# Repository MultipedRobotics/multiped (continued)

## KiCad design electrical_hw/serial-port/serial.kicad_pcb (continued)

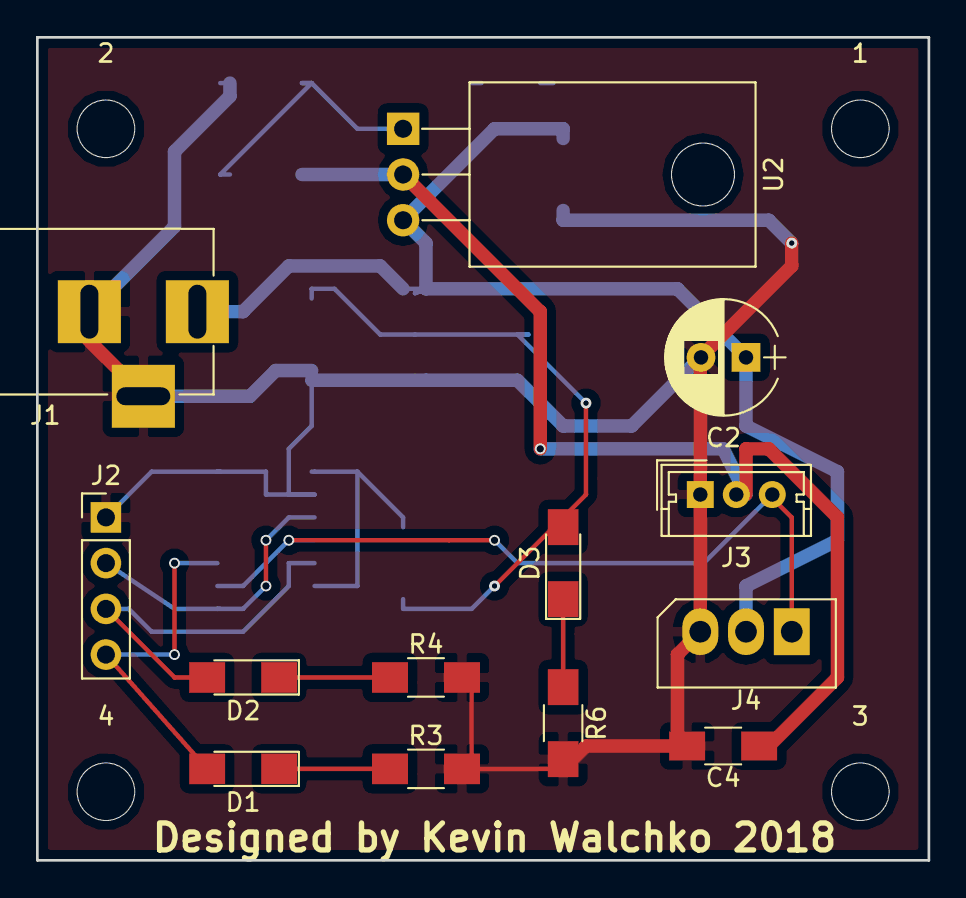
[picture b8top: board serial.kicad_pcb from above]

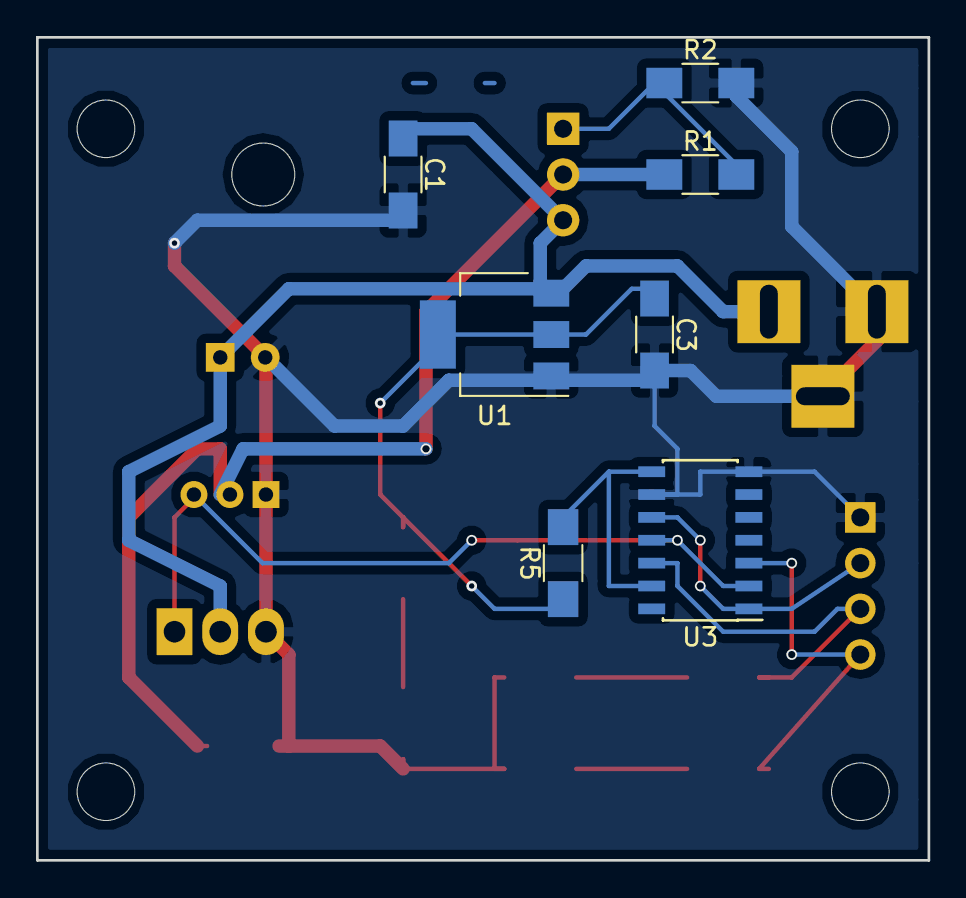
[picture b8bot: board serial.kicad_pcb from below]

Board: 2 copper layers, 49.5 x 45.7 mm, 24 parts (7 on the bottom side), 13 nets.

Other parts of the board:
1, 2, 3, 4: MountingHole_3.2mm_M3

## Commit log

2017-07-10 init
2017-07-10 bulk move of docs folder
2017-07-10 refactor docs
2017-07-10 winning! :smiley_cat:
2017-07-10 update ... added hardware
2017-07-11 fixed test
2017-07-11 code cleanup
2017-07-11 codacy
2017-07-11 upate
2017-07-12 added new gaits
2017-07-13 robot?
2017-07-13 readme and bin fix
2017-07-13 creating classes
2017-07-20 jupyter notebook
2017-12-03 working
2017-12-03 removed numpy
2017-12-25 reorg ... test still fail
2018-02-04 image link
2018-02-04 hardware updates
2018-02-04 pi zero clean-up
2018-02-04 fix build script
2018-02-04 readme.fix
2018-02-04 new pic :tada:
2018-02-04 wrong format
2018-02-04 readme update
2018-02-10 kicad
2018-02-23 new base
2018-02-25 pics moved
2018-02-25 pi docs
2018-02-25 updated docs
2018-02-25 reorg
2018-02-27 engine rename
2018-02-27 py2-3
2018-02-28 pics
2018-03-03 removed serial port kicad files
2018-03-03 reorg and clean up
2018-03-03 readme fix
2018-03-05 hw updates
2018-03-08 jst library
2018-03-09 electrical update
2018-03-09 new hw
2018-03-10 readme
2018-03-10 license
2018-03-10 found pic
2018-03-11 gait
2018-03-11 small fix
2018-03-12 new power board
2018-03-16 new new power board
2018-03-17 power 3 done :tada: :electric_plug:
2018-03-24 new head
2018-03-26 new leg design
2018-03-29 curved leg
2018-03-30 new tarsus
2018-04-02 new leg
2018-04-02 re-org and clean up :tada:
2018-04-09 tibia fix
2018-04-10 new power board v4
2018-04-19 power board
2018-04-22 update - 1 leg working
2018-04-23 new tibia
2018-04-23 clean out stl
2018-04-25 elect update
2018-04-29 jupyter update
2018-04-30 doc cleanup
2018-04-30 docs update
2018-04-30 working new head and power
2018-05-06 another new deck ... I think I like this :tada:
2018-05-06 seems to work :tada:
2018-05-07 new design :tada:
2018-05-07 Create deleteme
2018-05-09 new power board :electric_plug:
2018-05-09 test interface
2018-05-10 the stand
2018-05-15 pcb updates
2018-05-25 up and down ... nothing great
2018-06-10 power version 5 done and reorg
2018-06-11 multiped
2018-06-23 still not smooth, but looks like it works
2018-07-05 rework gait
2018-08-04 multiped test :smile:
2018-08-19 gecko updates
2018-08-26 more parts :bento:
2018-08-29 lidar base update v3 :smile:
2018-08-30 new pi base
2018-08-31 updated pi board
2018-08-31 rpi board update :bento:
2018-08-31 doc updates
2018-08-31 doc fix
2018-08-31 doc update :electric_plug:
2018-09-02 update requirements
2018-09-17 camera bracket
2018-09-17 new base with camera mount
2018-09-17 updated pi base :tada: :taco:
2018-09-17 readme updates
2018-09-23 moded head
2018-11-21 py3 :snake:
2018-11-26 removed tablet
2018-11-27 update/reorg/clean-up :snake:
